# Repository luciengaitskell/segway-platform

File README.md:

# Segway Platform
---
Self balancing and navigating robot

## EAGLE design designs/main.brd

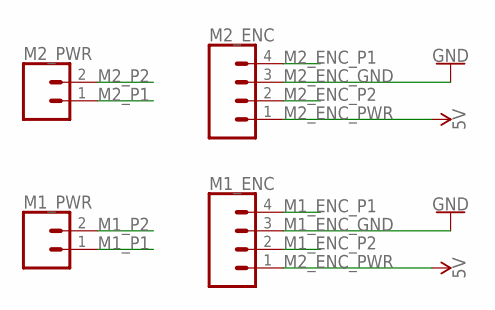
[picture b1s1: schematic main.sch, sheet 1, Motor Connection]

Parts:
M1_ENC, M2_ENC: CONN_04; 1X04
M1_PWR, M2_PWR: CONN_02PTH4; 1X02_XTRA_BIG

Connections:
M1_ENC_GND: M1_ENC.3
M1_ENC_P1: M1_ENC.4; also elsewhere on the board
M1_ENC_P2: M1_ENC.2; also elsewhere on the board
M1_P1: M1_PWR.1; also elsewhere on the board
M1_P2: M1_PWR.2; also elsewhere on the board
M2_ENC_GND: M2_ENC.3
M2_ENC_P1: M2_ENC.4; also elsewhere on the board
M2_ENC_P2: M2_ENC.2; also elsewhere on the board
M2_ENC_PWR: M1_ENC.1, M2_ENC.1
M2_P1: M2_PWR.1; also elsewhere on the board
M2_P2: M2_PWR.2; also elsewhere on the board

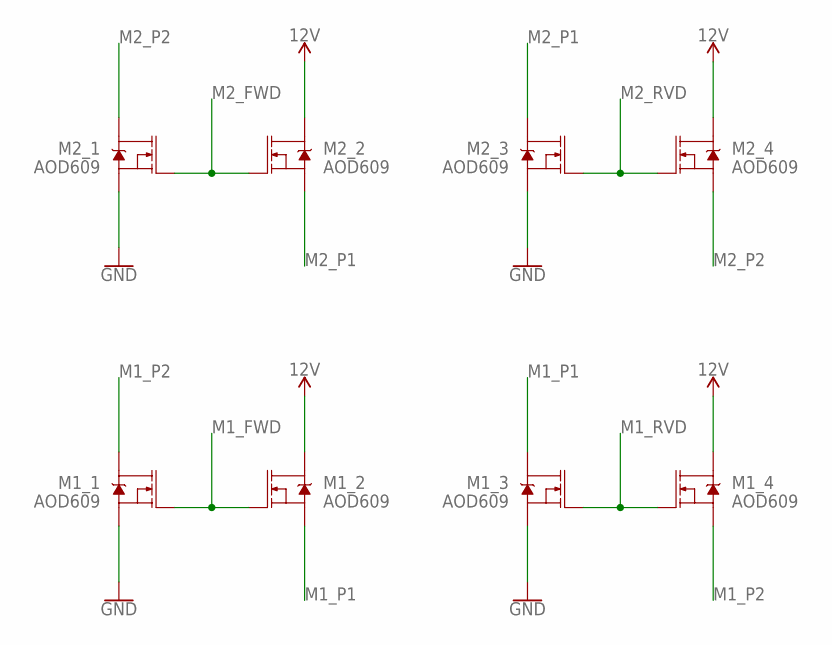
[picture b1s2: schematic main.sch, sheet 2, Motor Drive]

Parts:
M1_1, M1_2, M1_3, M1_4, M2_1, M2_2, M2_3, M2_4: AOD609; DPAK

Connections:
12V: M1_2.4 (D), M1_4.4 (D), M2_2.4 (D), M2_4.4 (D)
GND: M1_1.3 (S), M1_3.3 (S), M2_1.3 (S), M2_3.3 (S); also elsewhere on the board
M1_FWD: M1_1.1 (G), M1_2.1 (G); also elsewhere on the board
M1_P1: M1_2.3 (S), M1_3.4 (D); also elsewhere on the board
M1_P2: M1_1.4 (D), M1_4.3 (S); also elsewhere on the board
M1_RVD: M1_3.1 (G), M1_4.1 (G); also elsewhere on the board
M2_FWD: M2_1.1 (G), M2_2.1 (G); also elsewhere on the board
M2_P1: M2_2.3 (S), M2_3.4 (D); also elsewhere on the board
M2_P2: M2_1.4 (D), M2_4.3 (S); also elsewhere on the board
M2_RVD: M2_3.1 (G), M2_4.1 (G); also elsewhere on the board

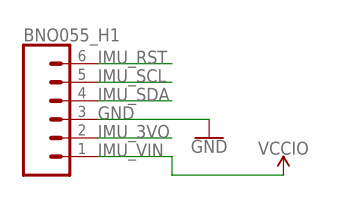
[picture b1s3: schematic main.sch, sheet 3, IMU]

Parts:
BNO055_H1: CONN_06SILK_FEMALE_PTH; 1X06

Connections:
GND: BNO055_H1.3; also elsewhere on the board
IMU_3VO: BNO055_H1.2
IMU_RST: BNO055_H1.6
IMU_SCL: BNO055_H1.5; also elsewhere on the board
IMU_SDA: BNO055_H1.4; also elsewhere on the board
IMU_VIN: BNO055_H1.1

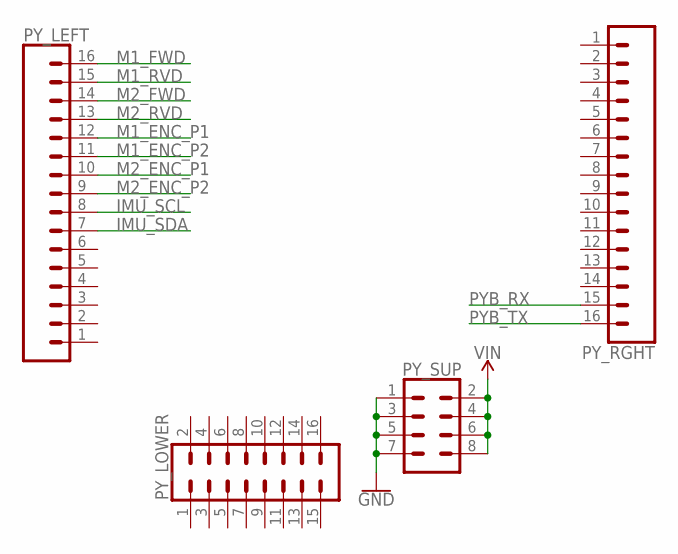
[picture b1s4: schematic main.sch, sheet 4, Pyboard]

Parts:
PY_LEFT: CONN_16; 1X16
PY_LOWER: CONN_08X2; 2X8
PY_RGHT: CONN_16; 1X16
PY_SUP: CONN_04X2; 2X4

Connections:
GND: PY_SUP.1, PY_SUP.3, PY_SUP.5, PY_SUP.7; also elsewhere on the board
IMU_SCL: PY_LEFT.8; also elsewhere on the board
IMU_SDA: PY_LEFT.7; also elsewhere on the board
M1_ENC_P1: PY_LEFT.12; also elsewhere on the board
M1_ENC_P2: PY_LEFT.11; also elsewhere on the board
M1_FWD: PY_LEFT.16; also elsewhere on the board
M1_RVD: PY_LEFT.15; also elsewhere on the board
M2_ENC_P1: PY_LEFT.10; also elsewhere on the board
M2_ENC_P2: PY_LEFT.9; also elsewhere on the board
M2_FWD: PY_LEFT.14; also elsewhere on the board
M2_RVD: PY_LEFT.13; also elsewhere on the board
PYB_RX: PY_RGHT.15; also elsewhere on the board
PYB_TX: PY_RGHT.16; also elsewhere on the board
VIN: PY_SUP.2, PY_SUP.4, PY_SUP.6, PY_SUP.8

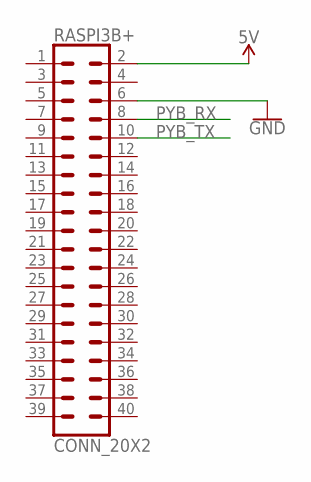
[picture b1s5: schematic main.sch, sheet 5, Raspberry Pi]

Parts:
RASPI3B+: CONN_20X2; 2X20

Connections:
5V: RASPI3B+.2
GND: RASPI3B+.6; also elsewhere on the board
PYB_RX: RASPI3B+.8; also elsewhere on the board
PYB_TX: RASPI3B+.10; also elsewhere on the board

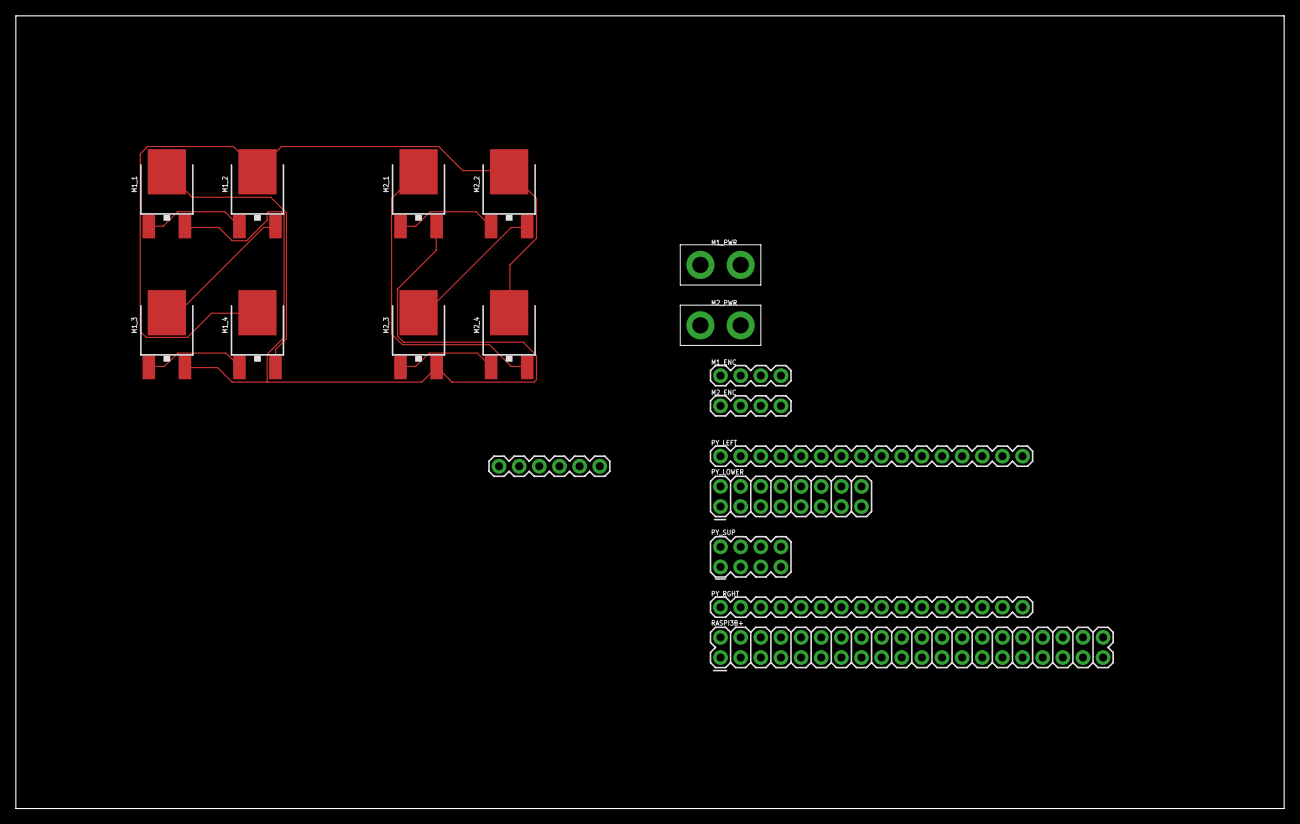
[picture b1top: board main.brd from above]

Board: 2 copper layers, 160.0 x 100.0 mm, 18 parts (0 on the bottom side), 20 nets.

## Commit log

2019-03-16 Add README
2019-03-16 Add gitignore
2019-03-16 Add code folders
2019-03-16 Add Eagle CAD setup
2019-03-16 Add initial electronics design

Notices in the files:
parts and their libraries:
SparkFun-DiscreteSemi: Licensing: Creative Commons ShareAlike 4.0 International - https://creativecommons.org/licenses/by-sa/4.0
